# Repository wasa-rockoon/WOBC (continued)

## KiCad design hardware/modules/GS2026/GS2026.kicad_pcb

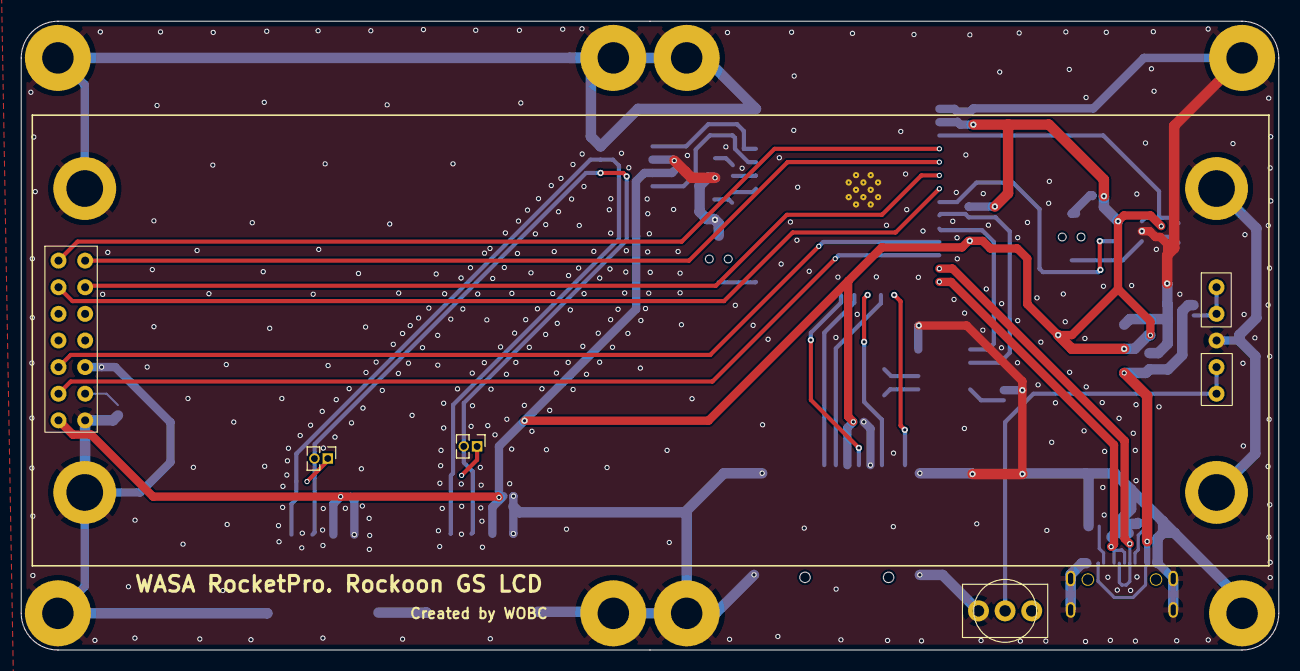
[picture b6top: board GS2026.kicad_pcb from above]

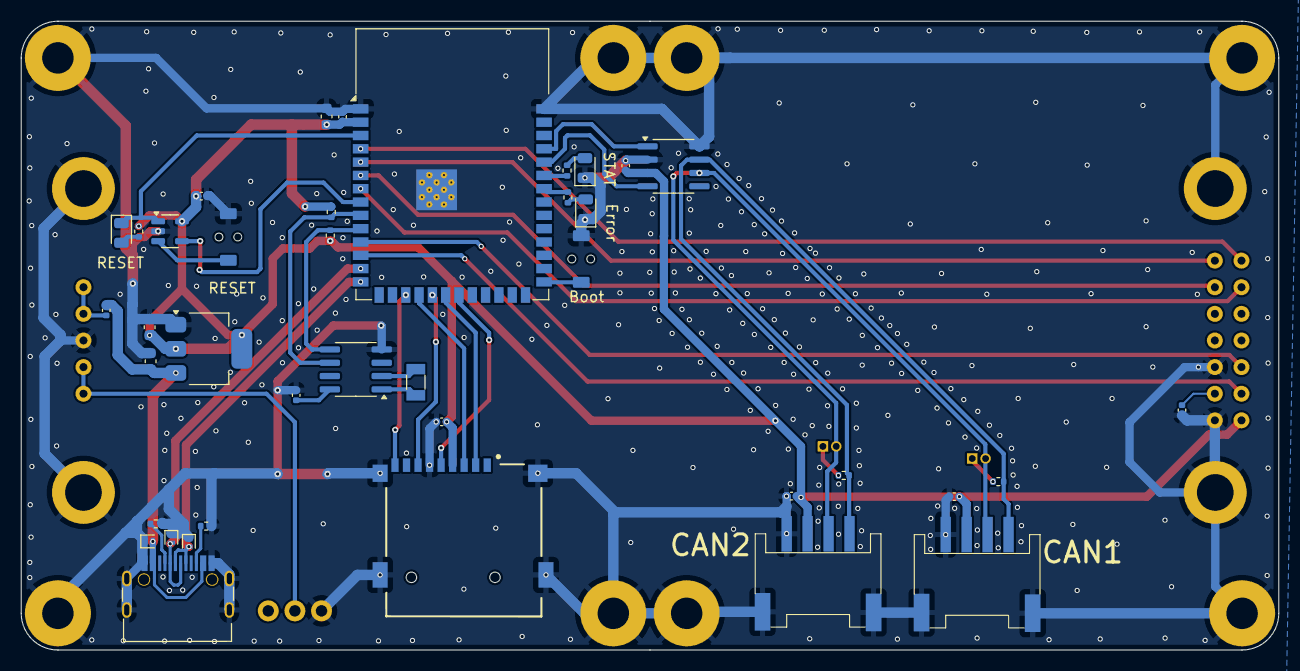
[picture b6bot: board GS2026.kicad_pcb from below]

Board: 2 copper layers, 120.0 x 60.0 mm, 44 parts (39 on the bottom side), 41 nets.

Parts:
B101: Board_2U_120x60
C101, C102, C203: 10uF; C_0603_1608Metric
C201, C202, C204, C301, C401, C602: 100nF; C_0402_1005Metric
C601: 10uF; C_0402_1005Metric
D201, D202, D203: 5V; D_SOD-882
D204: RESET; LED_0805_2012Metric
D205: ERROR; LED_0805_2012Metric
D206: STAT; LED_0805_2012Metric
J301, J401: Jumper; PinHeader_1x02_P1.27mm_Vertical
J302, J402: Conn_01x04_MountingPin; Grove_4P_L_SMD
MICRO_SD601: TF-01A
R201, R202: 5.1k; R_0402_1005Metric
R203, R204, R206: 470; R_0402_1005Metric
R205, R207: 10k; R_0402_1005Metric
R301, R401: 120; R_0402_1005Metric
R501: 1k; C_0402_1005Metric
R502: 68; C_0402_1005Metric
SW201: RESET_sw; TVAF06-A020B-R
SW202: RESET; TVAF06-A020B-R
SW501: sw1; ToggleSwitch
U101: AMS1117-3.3; SOT-223-3_TabPin2
U201: TPS3820; SOT-23-5
U202: SN65HVD230; SOIC-8_3.9x4.9mm_P1.27mm
U203: ESP32-S3-WROOM-1
U601: PCF8563T; SOIC-8_3.9x4.9mm_P1.27mm
USB201: USB_C_Receptacle_USB2.0; USB_C_TYPEC-301S-ACP16X7
Y601: Crystal; Crystal_SMD_3215-2Pin_3.2x1.5mm
lcd501: SC2004CSWB-XA-LB-G; SC2004CSWB

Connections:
+BATT: C602.2, U601.8 (VDD)
/CAN/CANH: J302.1, J402.1, R301.2, R401.2, U202.7 (CANH)
/CAN/CANL: J301.2, J302.2, J401.2, J402.2, U202.6 (CANL)
/ESP32S3/CAN_RX: U202.4 (R), U203.36 (U0RXD/GPIO44/CLK_OUT2)
/ESP32S3/CAN_TX: U202.1 (D), U203.37 (U0TXD/GPIO43/CLK_OUT1)
/ESP32S3/GPIO4/ADC1_CH3: U203.4 (GPIO4/TOUCH4/ADC1_CH3), lcd501.14 (DB7)
/ESP32S3/GPIO5/ADC1_CH4: U203.5 (GPIO5/TOUCH5/ADC1_CH4), lcd501.13 (DB6)
/ESP32S3/GPIO6/ADC1_CH5: U203.6 (GPIO6/TOUCH6/ADC1_CH5), lcd501.11 (DB4)
/ESP32S3/GPIO7/ADC1_CH6: U203.7 (GPIO7/TOUCH7/ADC1_CH6), lcd501.12 (DB5)
/ESP32S3/GPIO8/ADC1_CH7: U203.12 (GPIO8/TOUCH8/ADC1_CH7/SUBSPICS1), lcd501.4 (RS)
/ESP32S3/GPIO9/ADC1_CH8: MICRO_SD601.CD1 (CD), U203.17 (GPIO9/TOUCH9/ADC1_CH8/FSPIHD/SUBSPIHD)
/ESP32S3/GPIO10/ADC1_CH9: MICRO_SD601.3 (CMD), U203.18 (GPIO10/TOUCH10/ADC1_CH9/FSPICS0/FSPIIO4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)
/ESP32S3/GPIO11: MICRO_SD601.7 (DAT0), U203.19 (GPIO11/TOUCH11/ADC2_CH0/FSPID/FSPIIO5/S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)
/ESP32S3/GPIO12: MICRO_SD601.2 (CD/DAT3), U203.20 (GPIO12/TOUCH12/ADC2_CH1/FSPICLK/FSPIIO6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)
/ESP32S3/GPIO13: MICRO_SD601.5 (CLK), U203.21 (GPIO13/TOUCH13/ADC2_CH2/FSPIQ/FSPIIO7/S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)
/ESP32S3/GPIO18: U203.11 (GPIO18/U1RXD/ADC2_CH7/CLK_OUT3), lcd501.6 (E)
/ESP32S3/I2C_SCL: R205.2, U203.9 (GPIO16/U0CTS/ADC2_CH5/XTAL_32K_N), U601.6 (SCL)
/ESP32S3/I2C_SDA: R207.2, U203.10 (GPIO17/U1TXD/ADC2_CH6), U601.5 (SDA)
/ESP32S3/USB_D+: D202.2 (A2), U203.14 (GPIO20/U1CTS/ADC2_CH9/CLK_OUT1/USB_D+), USB201.A6 (D+), USB201.B6 (D+)
/ESP32S3/USB_D-: D203.2 (A2), U203.13 (GPIO19/U1RTS/ADC2_CH8/CLK_OUT2/USB_D-), USB201.A7 (D-), USB201.B7 (D-)
/ESP32S3/WDI: U201.4 (WDI), U203.8 (GPIO15/U0RTS/ADC2_CH4/XTAL_32K_P)
GND: B101.GND, C101.2, C102.2, C201.1, C202.1, C203.1, C204.2, C301.1, C401.1, C601.2, C602.1, D201.1 (A1), D202.1 (A1), D203.1 (A1), D205.1 (K), D206.1 (K), J302.4, J302.MP (MountPin), J402.4, J402.MP (MountPin), MICRO_SD601.6 (VSS), MICRO_SD601.MP1 (SHIELD), MICRO_SD601.MP2 (SHIELD), MICRO_SD601.MP3 (SHIELD), MICRO_SD601.MP4 (SHIELD), R201.2, R202.2, R501.1, SW201.2, SW202.2, SW501.3 (C), U101.1 (GND), U201.2 (GND), U202.2 (GND), U202.8 (Rs), U203.1 (GND), U203.40 (GND), U203.41 (GND), U601.4 (VSS), USB201.A1 (GND), USB201.A12 (GND), USB201.B1 (GND), USB201.B12 (GND), USB201.S1 (SHIELD), lcd501.1 (VSS), lcd501.5 (R/W), lcd501.16, lcd501.GND
unnamed: D204.2 (A), R203.2
unnamed: D205.2 (A), R204.2
unnamed: D206.2 (A), R206.2
unnamed: J301.1, R301.1
unnamed: J401.1, R401.1
unnamed: SW501.2 (B), lcd501.17 (K)
unnamed: SW201.1, U201.3 (MR)
unnamed: SW202.1, U203.27 (GPIO0/BOOT)
unnamed: R204.1, U203.34 (MTDI/GPIO41/CLK_OUT1)
unnamed: R206.1, U203.35 (MTMS/GPIO42)
unnamed: U601.1 (OSCI), Y601.1
unnamed: U601.2 (OSCO), Y601.2
unnamed: R201.1, USB201.A5 (CC1)
unnamed: R202.1, USB201.B5 (CC2)
unnamed: R502.1, lcd501.15 (A)
unnamed: R501.2, lcd501.3 (Vo)
RESET: D204.1 (K), U201.1 (RESET), U203.3 (EN)
VBUS: C101.1, D201.2 (A2), R502.2, U101.3 (VI), USB201.A4 (VBUS), USB201.A9 (VBUS), USB201.B4 (VBUS), USB201.B9 (VBUS)
VDD: C102.1, C201.2, C202.2, C203.2, C204.1, C301.2, C401.2, C601.1, J302.3, J402.3, MICRO_SD601.4 (VDD), R203.1, R205.1, R207.1, U101.2 (VO), U201.5 (VDD), U202.3 (VCC), U203.2 (3V3), lcd501.2 (VDD)

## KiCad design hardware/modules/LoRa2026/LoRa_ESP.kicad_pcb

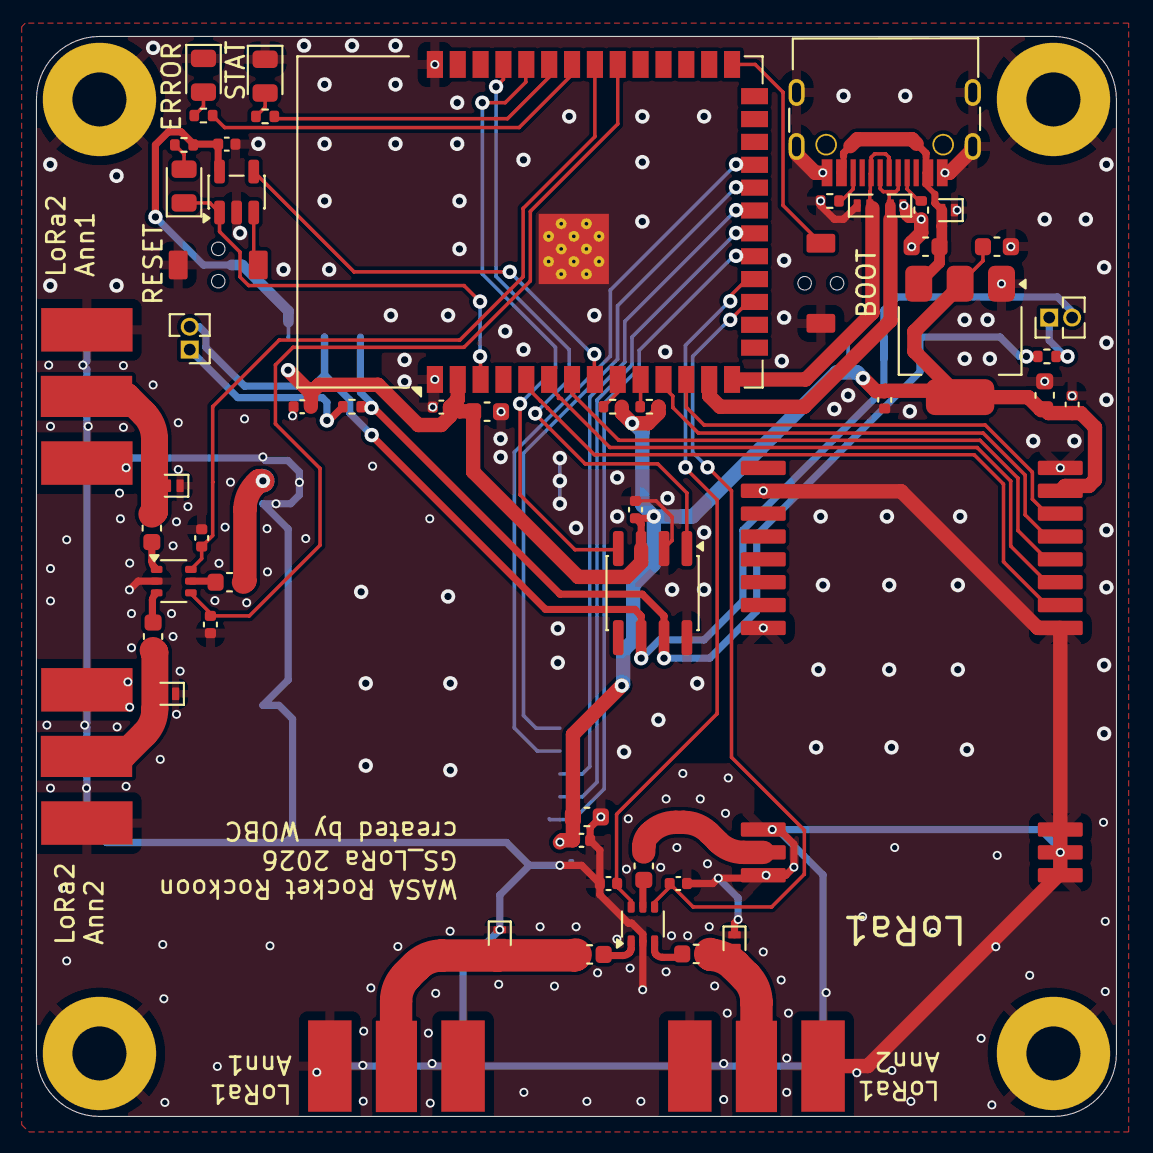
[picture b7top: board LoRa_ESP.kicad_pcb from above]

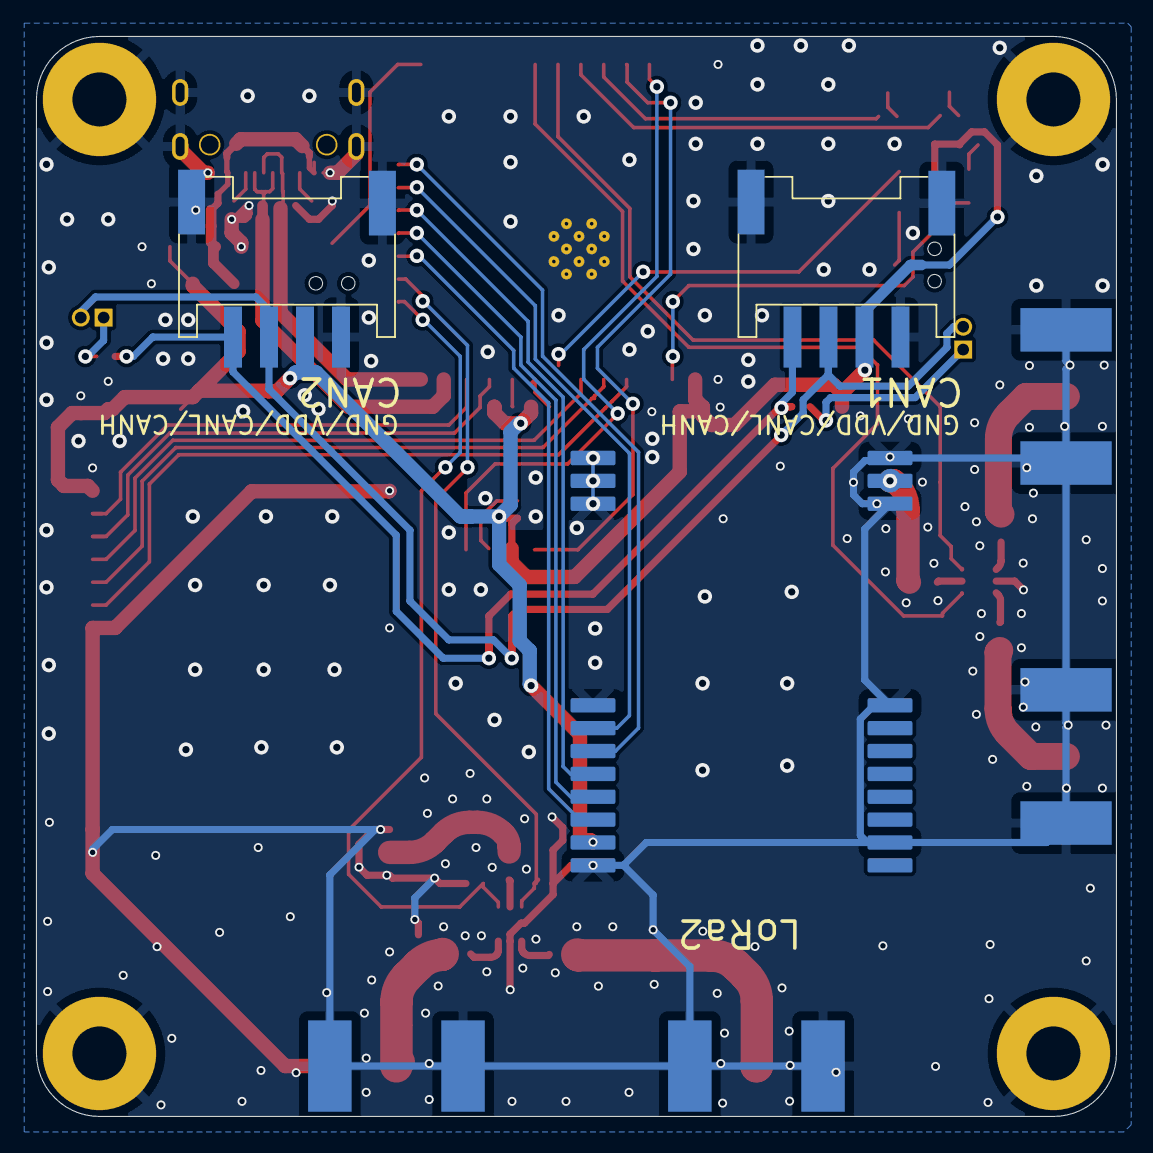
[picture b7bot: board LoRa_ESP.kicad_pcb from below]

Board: 2 copper layers, 60.0 x 60.0 mm, 60 parts (3 on the bottom side), 50 nets.

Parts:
BOOT: RESET; TVAF06-A020B-R
C101, C102, C306, C406: 10u; C_0603_1608Metric
C202, C602, C701, C702, C704: 100nF; C_0402_1005Metric
C301, C302, C305, C401, C402, C405: 100p; C_0603_1608Metric
C303, C304, C307, C403, C404, C407: 100n; C_0402_1005Metric
C703: 10uF; C_0603_1608Metric
D301, D302, D401, D402: ESD9B5.0ST5G; D_SOD-882
D701, D702, D703: 5V; D_SOD-882
D704: RESET; LED_0805_2012Metric
D705: ERROR; LED_0805_2012Metric
D706: STAT; LED_0805_2012Metric
J202, J602: Jumper; PinHeader_1x02_P1.27mm_Vertical
J203, J603: Conn_01x04_MountingPin; Grove_4P_L_SMD
J301, J302, J401, J402: SMA; SMA_aki
R202, R602: 120; R_0402_1005Metric
R701, R702: 5.1k; R_0402_1005Metric
R703, R704, R706: 470; R_0402_1005Metric
R705, R707: 10k; R_0402_1005Metric
RESET: RESET_sw; TVAF06-A020B-R
Switch301, Switch401: XA17-G4K1; SOT-363_SC-70-6
U101: AMS1117-3.3; SOT-223-3_TabPin2
U301, U401: E220-900T22S(JP)
U701: TPS3820; SOT-23-5
U702: SN65HVD230; SOIC-8_3.9x4.9mm_P1.27mm
U703: ESP32-S3-WROOM-1
USB701: USB_C_Receptacle_USB2.0; USB_C_TYPEC-301S-ACP16X7

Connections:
/ESP32core/CANH: J203.1, J603.1, R202.2, R602.2, U702.7 (CANH)
/ESP32core/CANL: J202.2, J203.2, J602.2, J603.2, U702.6 (CANL)
/ESP32core/CAN_RX: U702.4 (R), U703.36 (U0RXD/GPIO44/CLK_OUT2)
/ESP32core/CAN_TX: U702.1 (D), U703.37 (U0TXD/GPIO43/CLK_OUT1)
/ESP32core/GPIO5/ADC1_CH4: U401.5 (M0), U703.5 (GPIO5/TOUCH5/ADC1_CH4)
/ESP32core/GPIO6/ADC1_CH5: U401.6 (M1), U703.6 (GPIO6/TOUCH6/ADC1_CH5)
/ESP32core/GPIO7/ADC1_CH6: U401.7 (RXD), U703.7 (GPIO7/TOUCH7/ADC1_CH6)
/ESP32core/GPIO8/ADC1_CH7: U401.9 (AUX), U703.12 (GPIO8/TOUCH8/ADC1_CH7/SUBSPICS1)
/ESP32core/GPIO9/ADC1_CH8: C404.1, Switch401.4 (V1), U703.17 (GPIO9/TOUCH9/ADC1_CH8/FSPIHD/SUBSPIHD)
/ESP32core/GPIO10/ADC1_CH9: C403.1, Switch401.6 (V2), U703.18 (GPIO10/TOUCH10/ADC1_CH9/FSPICS0/FSPIIO4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)
/ESP32core/GPIO11: U301.9 (AUX), U703.19 (GPIO11/TOUCH11/ADC2_CH0/FSPID/FSPIIO5/S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)
/ESP32core/GPIO12: U301.8 (TXD), U703.20 (GPIO12/TOUCH12/ADC2_CH1/FSPICLK/FSPIIO6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)
/ESP32core/GPIO13: U301.7 (RXD), U703.21 (GPIO13/TOUCH13/ADC2_CH2/FSPIQ/FSPIIO7/S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)
/ESP32core/GPIO14: U301.5 (M0), U703.22 (GPIO14/TOUCH14/ADC2_CH3/FSPIWP/FSPIDQS/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)
/ESP32core/GPIO18: U401.8 (TXD), U703.11 (GPIO18/U1RXD/ADC2_CH7/CLK_OUT3)
/ESP32core/GPIO21: U301.6 (M1), U703.23 (GPIO21)
/ESP32core/GPIO39: C304.1, Switch301.4 (V1), U703.32 (MTCK/GPIO39/CLK_OUT3/SUBSPICS1)
/ESP32core/GPIO40: C303.1, Switch301.6 (V2), U703.33 (MTDO/GPIO40/CLK_OUT2)
/ESP32core/I2C_SCL: R705.2, U703.9 (GPIO16/U0CTS/ADC2_CH5/XTAL_32K_N)
/ESP32core/I2C_SDA: R707.2, U703.10 (GPIO17/U1TXD/ADC2_CH6)
/ESP32core/USB_D+: D702.2 (A2), U703.14 (GPIO20/U1CTS/ADC2_CH9/CLK_OUT1/USB_D+), USB701.A6 (D+), USB701.B6 (D+)
/ESP32core/USB_D-: D703.2 (A2), U703.13 (GPIO19/U1RTS/ADC2_CH8/CLK_OUT2/USB_D-), USB701.A7 (D-), USB701.B7 (D-)
/ESP32core/WDI: U701.4 (WDI), U703.8 (GPIO15/U0RTS/ADC2_CH4/XTAL_32K_P)
GND: BOOT.2, C101.2, C102.2, C202.1, C303.2, C304.2, C306.2, C307.2, C403.2, C404.2, C406.2, C407.2, C602.1, C701.1, C702.1, C703.1, C704.2, D301.1 (A1), D302.1 (A1), D401.1 (A1), D402.1 (A1), D701.1 (A1), D702.1 (A1), D703.1 (A1), D705.1 (K), D706.1 (K), J203.4, J203.MP (MountPin), J301.2 (Ext), J302.2 (Ext), J401.2 (Ext), J402.2 (Ext), J603.4, J603.MP (MountPin), R701.2, R702.2, RESET.2, Switch301.2 (GND), Switch401.2 (GND), U101.1 (GND), U301.1 (GND), U301.2 (GND), U301.3 (GND), U301.4 (GND), U301.11 (GND), U301.13 (GND), U301.19 (GND), U301.20 (GND), U301.22 (GND), U401.1 (GND), U401.2 (GND), U401.3 (GND), U401.4 (GND), U401.11 (GND), U401.13 (GND), U401.19 (GND), U401.20 (GND), U401.22 (GND), U701.2 (GND), U702.2 (GND), U702.8 (Rs), U703.1 (GND), U703.40 (GND), U703.41 (GND), USB701.A1 (GND), USB701.A12 (GND), USB701.B1 (GND), USB701.B12 (GND), USB701.S1 (SHIELD)
unnamed: C301.2, D301.2 (A2), J301.1 (In)
unnamed: C302.2, D302.2 (A2), J302.1 (In)
unnamed: C401.2, D401.2 (A2), J401.1 (In)
unnamed: C402.2, D402.2 (A2), J402.1 (In)
unnamed: D704.2 (A), R703.2
unnamed: D705.2 (A), R704.2
unnamed: D706.2 (A), R706.2
unnamed: J202.1, R202.1
unnamed: J602.1, R602.1
unnamed: C305.2, Switch301.5 (J1)
unnamed: C302.1, Switch301.3 (J2)
unnamed: C301.1, Switch301.1 (J3)
unnamed: C405.2, Switch401.5 (J1)
unnamed: C402.1, Switch401.3 (J2)
unnamed: C401.1, Switch401.1 (J3)
unnamed: C305.1, U301.21 (ANT)
unnamed: C405.1, U401.21 (ANT)
unnamed: RESET.1, U701.3 (MR)
unnamed: BOOT.1, U703.27 (GPIO0/BOOT)
unnamed: R704.1, U703.34 (MTDI/GPIO41/CLK_OUT1)
unnamed: R706.1, U703.35 (MTMS/GPIO42)
unnamed: R701.1, USB701.A5 (CC1)
unnamed: R702.1, USB701.B5 (CC2)
RESET: D704.1 (K), U701.1 (RESET), U703.3 (EN)
VBUS: C101.1, D701.2 (A2), U101.3 (VI), USB701.A4 (VBUS), USB701.A9 (VBUS), USB701.B4 (VBUS), USB701.B9 (VBUS)
VDD: C102.1, C202.2, C306.1, C307.1, C406.1, C407.1, C602.2, C701.2, C702.2, C703.2, C704.1, J203.3, J603.3, R703.1, R705.1, R707.1, U101.2 (VO), U301.10 (VDD), U401.10 (VDD), U701.5 (VDD), U702.3 (VCC), U703.2 (3V3)

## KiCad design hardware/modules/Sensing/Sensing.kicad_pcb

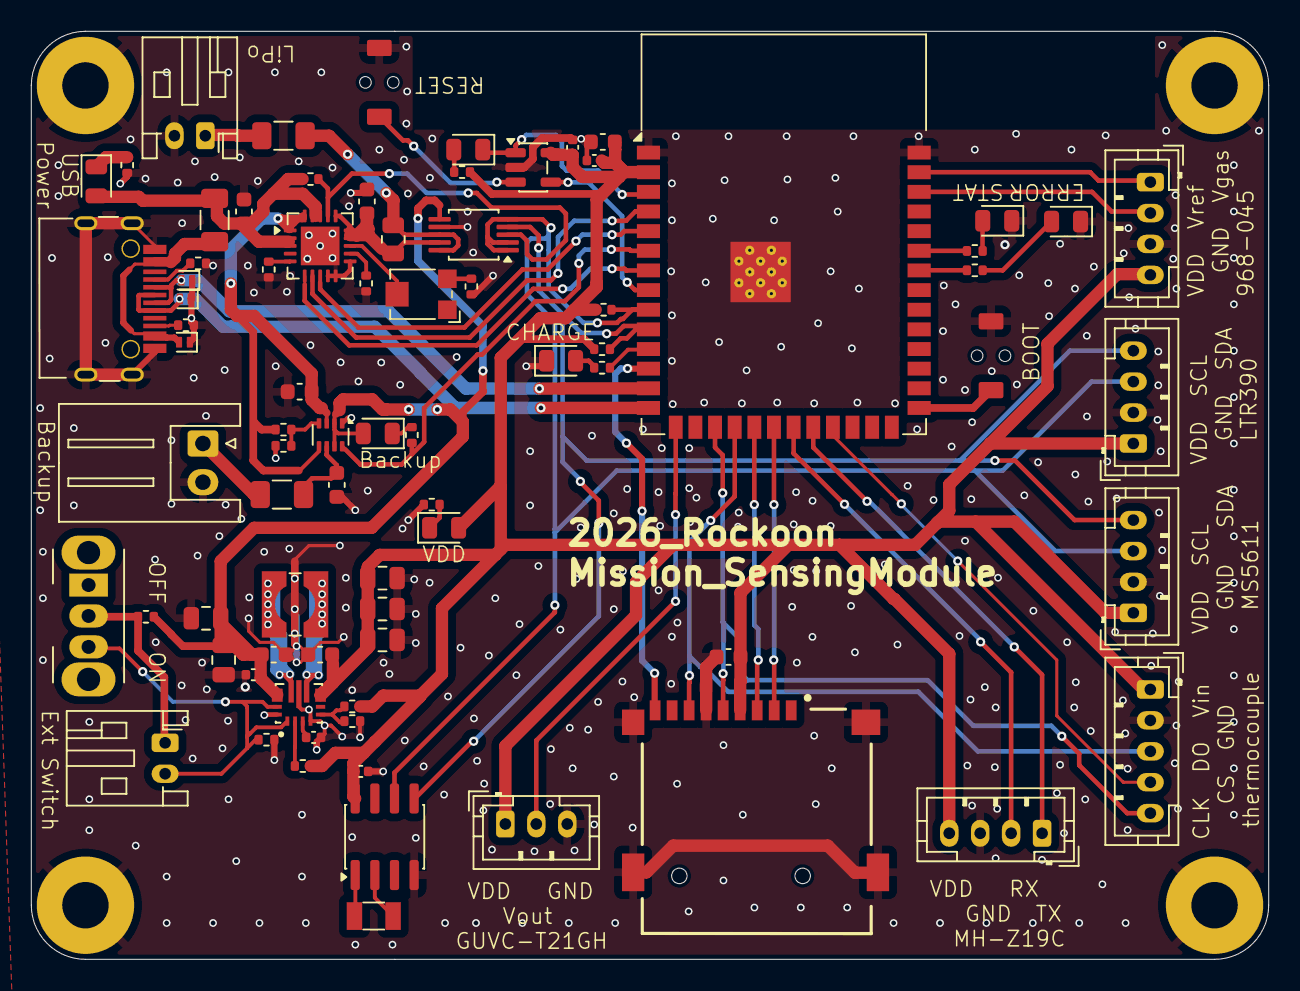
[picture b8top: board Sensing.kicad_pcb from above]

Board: 2 copper layers, 80.0 x 60.0 mm, 79 parts (0 on the bottom side), 61 nets.

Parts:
B101: Board_1U_60x60
C201, C203, C308, C309, C402: 100nF; C_0402_1005Metric
C202, C301, C302, C303, C306, C307, C310, C401: 10uF; C_0603_1608Metric
C304, C305, C311, C312, C313: 10uF; C_0805_2012Metric
D201, D202, D203: 5V; D_SOD-882
D204: RESET; LED_0805_2012Metric
D205: ERROR; LED_0805_2012Metric
D206: STAT; LED_0805_2012Metric
F301, F302, F303: Polyfuse; Fuse_1206_3216Metric
J101: MH-Z19C; JST_PH_B4B-PH-K_1x04_P2.00mm_Vertical
J102: 熱電対; JST_PH_B5B-PH-K_1x05_P2.00mm_Vertical
J103: GUVC-T21GH; JST_PH_B3B-PH-K_1x03_P2.00mm_Vertical
J104: MS5611 (MS5607); JST_PH_B4B-PH-K_1x04_P2.00mm_Vertical
J105: LTR390; JST_PH_B4B-PH-K_1x04_P2.00mm_Vertical
J106: 968-046; JST_PH_B4B-PH-K_1x04_P2.00mm_Vertical
J301: Battery; JST_XH_S2B-XH-A_1x02_P2.50mm_Horizontal
J302: Ext Switch; JST_PH_S2B-PH-K_1x02_P2.00mm_Horizontal
J303: LiPo; JST_PH_S2B-PH-K_1x02_P2.00mm_Horizontal
L301: L; L_Wuerth_WE-TPC-3816
LED301: USB Power; LED_0805_2012Metric
LED302: Backup; LED_0805_2012Metric
LED303: CHARGE; LED_0805_2012Metric
LED304: VDD; LED_0805_2012Metric
MICRO_SD401: TF-01A
R201, R202: 5.1k; R_0402_1005Metric
R203, R204, R206: 470; R_0402_1005Metric
R205, R207: 4.7k; R_0402_1005Metric
R301, R302, R308, R310, R316: 1k; R_0402_1005Metric
R303, R306, R307, R311, R313: 100k; R_0402_1005Metric
R304, R309: 10k; R_0402_1005Metric
R305, R315: 47k; R_0402_1005Metric
R312: 50mΩ; R_0805_2012Metric
R314: 15k; R_0402_1005Metric
RV301: 10k; Potentiometer_Bourns_TC33X_Vertical
SW201: RESET_sw; TVAF06-A020B-R
SW202: BOOT_sw; TVAF06-A020B-R
SW301: Power Switch; SW_Slide_SPDT_Angled_CK_OS102011MA1Q
U201: TPS3820; SOT-23-5
U202: ESP32-S3-WROOM-1
U301: MCP73871-1CC; QFN-20-1EP_4x4mm_P0.5mm_EP2.5x2.5mm
U302: TPS2116DRL; SOT-583-8
U303: TPS63070RNMR; VREG_TPS63070RNMR
U304: INA226; VSSOP-10_3x3mm_P0.5mm
U401: PCF8563T; SOIC-8_3.9x4.9mm_P1.27mm
USB201: USB_C_Receptacle_USB2.0; USB_C_TYPEC-301S-ACP16X7
Y401: Crystal; Crystal_SMD_3215-2Pin_3.2x1.5mm

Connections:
/ESP32S3/GPIO1/ADC1_CH0: J106.1, U202.39 (GPIO1/TOUCH1/ADC1_CH0)
/ESP32S3/GPIO2/ADC1_CH1: J106.2, U202.38 (GPIO2/TOUCH2/ADC1_CH1)
/ESP32S3/GPIO3/ADC1_CH2: J103.2, U202.15 (GPIO3/TOUCH3/ADC1_CH2)
/ESP32S3/GPIO4/ADC1_CH3: U202.4 (GPIO4/TOUCH4/ADC1_CH3), U301.7 (STAT2)
/ESP32S3/GPIO5/ADC1_CH4: U202.5 (GPIO5/TOUCH5/ADC1_CH4), U301.8 (STAT1/~LBO)
/ESP32S3/GPIO6/ADC1_CH5: R308.2, U202.6 (GPIO6/TOUCH6/ADC1_CH5), U302.8 (ST)
/ESP32S3/GPIO7/ADC1_CH6: U202.7 (GPIO7/TOUCH7/ADC1_CH6), U301.6 (~PG)
/ESP32S3/GPIO8/ADC1_CH7: MICRO_SD401.CD1 (CD), U202.12 (GPIO8/TOUCH8/ADC1_CH7/SUBSPICS1)
/ESP32S3/GPIO9/ADC1_CH8: J102.5, MICRO_SD401.5 (CLK), U202.17 (GPIO9/TOUCH9/ADC1_CH8/FSPIHD/SUBSPIHD)
/ESP32S3/GPIO10/ADC1_CH9: J102.3, MICRO_SD401.7 (DAT0), U202.18 (GPIO10/TOUCH10/ADC1_CH9/FSPICS0/FSPIIO4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)
/ESP32S3/GPIO11: MICRO_SD401.3 (CMD), U202.19 (GPIO11/TOUCH11/ADC2_CH0/FSPID/FSPIIO5/S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)
/ESP32S3/GPIO12: MICRO_SD401.2 (CD/DAT3), U202.20 (GPIO12/TOUCH12/ADC2_CH1/FSPICLK/FSPIIO6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)
/ESP32S3/GPIO18: R310.2, U202.11 (GPIO18/U1RXD/ADC2_CH7/CLK_OUT3)
/ESP32S3/GPIO21: J102.4, U202.23 (GPIO21)
/ESP32S3/USB_D+: D202.2 (A2), U202.14 (GPIO20/U1CTS/ADC2_CH9/CLK_OUT1/USB_D+), USB201.A6 (D+), USB201.B6 (D+)
/ESP32S3/USB_D-: D203.2 (A2), U202.13 (GPIO19/U1RTS/ADC2_CH8/CLK_OUT2/USB_D-), USB201.A7 (D-), USB201.B7 (D-)
/ESP32S3/VUSB: D201.2 (A2), F301.1, USB201.A4 (VBUS), USB201.A9 (VBUS), USB201.B4 (VBUS), USB201.B9 (VBUS)
/ESP32S3/WDI: U201.4 (WDI), U202.8 (GPIO15/U0RTS/ADC2_CH4/XTAL_32K_P)
/RX: J101.2, U202.21 (GPIO13/TOUCH13/ADC2_CH2/FSPIQ/FSPIIO7/S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)
/SCL: J104.3, J105.3, R205.2, U202.9 (GPIO16/U0CTS/ADC2_CH5/XTAL_32K_N), U304.1 (A1), U304.2 (A0), U304.5 (SCL), U401.6 (SCL)
/SDA: J104.4, J105.4, R207.2, U202.10 (GPIO17/U1TXD/ADC2_CH6), U304.4 (SDA), U401.5 (SDA)
/TX: J101.1, U202.22 (GPIO14/TOUCH14/ADC2_CH3/FSPIWP/FSPIDQS/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)
GND: B101.GND, C201.1, C202.1, C203.2, C301.2, C302.2, C303.2, C304.2, C305.2, C306.2, C307.2, C308.2, C309.2, C310.2, C311.2, C312.2, C313.2, C401.2, C402.1, D201.1 (A1), D202.1 (A1), D203.1 (A1), D205.1 (K), D206.1 (K), J101.3, J102.2, J103.3, J104.2, J105.2, J106.3, J301.2, J303.2, LED303.1 (K), MICRO_SD401.6 (VSS), MICRO_SD401.MP1 (SHIELD), MICRO_SD401.MP2 (SHIELD), MICRO_SD401.MP3 (SHIELD), MICRO_SD401.MP4 (SHIELD), R201.2, R202.2, R301.2, R302.2, R303.2, R304.1, R305.1, R311.2, R314.1, R316.2, SW201.2, SW202.2, U201.2 (GND), U202.1 (GND), U202.40 (GND), U202.41 (GND), U301.9 (~TE), U301.10 (V_{SS}), U301.11 (V_{SS}), U301.21 (V_{SS}), U302.1 (GND), U303.4 (GND), U303.10 (PGND), U303.15 (VSEL), U304.7 (GND), U401.4 (VSS), USB201.A1 (GND), USB201.A12 (GND), USB201.B1 (GND), USB201.B12 (GND), USB201.S1 (SHIELD)
unnamed: D204.2 (A), R203.2
unnamed: D205.2 (A), R204.2
unnamed: D206.2 (A), R206.2
unnamed: F302.1, J301.1
unnamed: J302.1, R309.2, SW301.2 (B)
unnamed: J302.2, R311.1, SW301.3 (C), U303.1 (PS/SYNC), U303.14 (EN)
unnamed: F303.1, J303.1
unnamed: C301.1, F301.2, LED301.2 (A), R306.1, U301.2 (VPCC), U301.3 (SEL), U301.18 (IN), U301.19 (IN)
unnamed: LED301.1 (K), R301.1
unnamed: C304.1, C305.1, C307.1, C308.1, LED302.2 (A), R309.1, U302.2 (VOUT), U302.7 (VOUT), U303.12_13 (VIN), U304.6 (VS)
unnamed: LED302.1 (K), R308.1
unnamed: LED303.2 (A), R310.1
unnamed: LED304.1 (K), R316.1
unnamed: R302.1, RV301.3
unnamed: SW201.1, U201.3 (MR)
unnamed: SW202.1, U202.27 (GPIO0/BOOT)
unnamed: R204.1, U202.34 (MTDI/GPIO41/CLK_OUT1)
unnamed: R206.1, U202.35 (MTMS/GPIO42)
unnamed: R306.2, U301.17 (CE), U304.3 (~Alert)
unnamed: RV301.2, U301.13 (PROG1)
unnamed: R303.1, U301.12 (PROG3)
unnamed: R304.2, U301.5 (THERM)
unnamed: C306.1, R312.1, U301.14 (V_{BAT}), U301.15 (V_{BAT}), U301.16 (V_{BAT_SENSE}), U304.9 (Vin-)
unnamed: C303.1, R307.1, U301.1 (OUT), U301.20 (OUT), U302.3 (VIN1), U302.5 (MODE)
unnamed: R305.2, R307.2, U302.4 (PR1)
unnamed: C302.1, F302.2, U302.6 (VIN2)
unnamed: R314.2, R315.1, U303.5 (FB)
unnamed: L301.1, U303.11 (L1)
unnamed: L301.2, U303.9 (L2)
unnamed: R313.2, U303.2 (PG)
unnamed: C309.1, U303.3 (VAUX)
unnamed: F303.2, R312.2, U304.8 (Vbus), U304.10 (Vin+)
unnamed: U401.1 (OSCI), Y401.1
unnamed: U401.2 (OSCO), Y401.2
unnamed: R201.1, USB201.A5 (CC1)
unnamed: R202.1, USB201.B5 (CC2)
RESET: D204.1 (K), U201.1 (RESET), U202.3 (EN)
VDD: C201.2, C202.2, C203.1, C310.1, C311.1, C312.1, C313.1, C401.1, C402.2, J101.4, J102.1, J103.1, J104.1, J105.1, J106.4, LED304.2 (A), MICRO_SD401.4 (VDD), R203.1, R205.1, R207.1, R313.1, R315.2, U201.5 (VDD), U202.2 (3V3), U303.7_8 (VOUT), U401.8 (VDD)

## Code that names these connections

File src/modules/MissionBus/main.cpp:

// #define NDEBUG

#include <library/wobc.h>
#include <components/LiPoPower/lipo_power.h>
#include <components/LoRa/lora.h>
#include <components/Pressure/pressure.h>
#include <components/IMU/IMU.h>
#include <components/GPS/gps.h>
#include <components/Logger/logger.h>
#include <components/Telemeter/telemeter.h>
#include <SPI.h>

#define SPI0_SCK_PIN 5
#define SPI0_MOSI_PIN 1
#define SPI0_MISO_PIN 2
#define SPI0_CS_PIN 4

#define SD_INSERTED_PIN 6
#define SDCARD_MOSI_PIN SPI0_MOSI_PIN
#define SDCARD_MISO_PIN SPI0_MISO_PIN
#define SDCARD_SS_PIN SPI0_CS_PIN
#define SDCARD_SCK_PIN SPI0_SCK_PIN

#define ST 8
#define PG 11
#define STAT1 10
#define STAT2 -1
#define HEAT 48
#define CHARGELED -1
#define TEMP 9

#define LORA_CHANNEL 37
#define LORA_TX_PIN 13
#define LORA_RX_PIN 12
#define LORA_AUX_PIN 21
#define LORA_M0_PIN 14
#define LORA_M1_PIN 18

// GS-compatible setting; verify against the MissionBus board wiring.
#define CAN_RX_PIN 44
#define CAN_TX_PIN 43

constexpr uint8_t module_id = 0x4D;
constexpr uint8_t unit_id = 0x62;

HardwareSerial lora_serial(1);
core::CANBus can_bus(CAN_RX_PIN, CAN_TX_PIN);
core::SerialBus serial_bus(Serial);
// Use the same telemetry server as GS, including IGN and sensor telemetry.
component::Telemeter telemeter(true);

component::LiPoPower power(Wire, ST, PG, STAT1, STAT2, HEAT, CHARGELED, TEMP, unit_id, 1);
component::LoRa lora(LORA_AUX_PIN, LORA_M0_PIN, LORA_M1_PIN, LORA_TX_PIN, LORA_RX_PIN, LORA_CHANNEL, 0);
component::Logger logger(SPI, SPI0_CS_PIN, SD_INSERTED_PIN);
component::Pressure pressure(Wire, unit_id);
component::IMU9 imu(Wire, unit_id, 10, IMU_DATA, IMU_BMI_BMM);
component::GPS gps(38, 39, 9600, unit_id);

interface::WatchIndicator<unsigned> status_indicator(42, kernel::packetCount());
interface::WatchIndicator<unsigned> error_indicator(41, kernel::errorCount());

class Main : public process::Component {
public:
    Main() : process::Component("main", 0x00) {}
    kernel::Listener my_listener_;

    void setup() override {
        my_listener_.telemetry(); 
        listen(my_listener_, 8);
    }

    void loop() override {
        while (my_listener_) {
            const wcpp::Packet packet = my_listener_.pop();
            auto im = packet.find("Im");
            if (!im) {
                wcpp::Packet lorapacket = newPacket(64);
                if (!lorapacket) continue;
                lorapacket.command(lora.send_command_id, lora.component_id_base + 0);
                lorapacket.append("Pa").setPacket(packet);
                sendPacket(lorapacket);
            }
        }
    }

} main_;

void setup() {
    Serial.begin(115200);
    kernel::setUnitId(unit_id);
    if (!kernel::begin(module_id, true)) return;

    Serial0.setPins(4, 5);
    Wire.begin(17, 16);

    SPI.begin(SDCARD_SCK_PIN, SDCARD_MISO_PIN, SDCARD_MOSI_PIN, SDCARD_SS_PIN);

    delay(1000); 

    status_indicator.begin();
    status_indicator.blink_on_change();

    error_indicator.begin();
    error_indicator.set(true);

    
    imu.begin();
    can_bus.begin();
    serial_bus.begin();
    telemeter.begin();
    power.begin();
    lora.begin();
    pressure.begin();
    gps.begin();
    logger.begin();
    main_.begin();

    error_indicator.set(false);
    error_indicator.blink_on_change(100);
}

void loop() {
    status_indicator.update();
    error_indicator.update();
}

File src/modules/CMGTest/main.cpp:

#include <Arduino.h>
#include <Wire.h>
#include <SPI.h>
#include <library/wobc.h>
#include <components/Logger/logger.h>
#include <components/IMU/IMU.h>
#include <components/Pressure/pressure.h>
#include <components/Heater/Heater.h>
#include <components/Servo/LogServo.h>
//#include <components/MotorControl/MotorControl.h>
#include <components/LiPoPower/lipo_power.h>
#include <components/PowerMeasure/PowerMeasure.h>


#define I2C_SCL_PIN 16
#define I2C_SDA_PIN 17
#define I2C_freq 400000

#define SPI0_SCK_PIN 12
#define SPI0_MOSI_PIN 11
#define SPI0_MISO_PIN 13
#define SPI0_CS_PIN 10

#define SD_INSERTED_PIN 9
#define SDCARD_MOSI_PIN SPI0_MOSI_PIN
#define SDCARD_MISO_PIN SPI0_MISO_PIN
#define SDCARD_SS_PIN SPI0_CS_PIN
#define SDCARD_SCK_PIN SPI0_SCK_PIN

#define ST 4
#define PG 5
#define STAT1 7
#define STAT2 6
#define HEAT 48
#define CHARGELED 18
#define TEMP 47

core::SerialBus serial_bus(Serial); 

constexpr uint8_t module_id = 0x45;
constexpr uint8_t unit_id = 0x66;

component::Logger logger(SPI, SPI0_CS_PIN, -1, 10.0);
component::IMU9 imu(Wire, unit_id, 100, IMU_DATA_WITH_KALMAN_6, IMU_ICM_MMC);
//component::Heater heater(Wire, unit_id, 1);
//component::LogServo servo(12, 34, unit_id, WITH_READANGLE, 50);
component::Pressure pressure(Wire, unit_id, 1);
//component::MotorControl motor(2, 3, unit_id, 1000, 50);
component::LiPoPower power(Wire, ST, PG, STAT1, STAT2, HEAT, CHARGELED, TEMP, unit_id, 1);
component::PowerMeasure power_measure(Wire, unit_id, 10);

interface::WatchIndicator<unsigned> status_indicator(42, kernel::packetCount());
interface::WatchIndicator<unsigned> error_indicator(41, kernel::errorCount());

class Main : public process::Component {
public:
    Main() : process::Component("Main", 0x00) {}
    kernel::Listener my_listener_;
    kernel::Listener heartbeat_;
  
    void setup() override {
        LOG("CMG Task: Setup started"); 
        my_listener_.telemetry(); 
        listen(my_listener_, 8);
        heartbeat_.component(0x4D);
        listen(heartbeat_,1);
        LOG("CMG Task: loop starts"); 
    }

    void loop() override {
        static uint32_t start_time = millis();
        if (millis() - start_time > 1200000) {
            request_file_split.store(true);
            start_time = millis();
        }
        delay(100);
        // while (my_listener_) { //main向けのログがあれば実行
            float Ax = 0.1;
            float Ay = 0.2;
            float Az = 0.3;
            float Gx = 0.4;
            float Gy = 0.5;
            float Gz = 0.6;
            float Mx = 0.7;
            float My = 0.8;
            float Mz = 0.9;
            wcpp::Packet packet = my_listener_.pop();
            wcpp::Packet new_packet = newPacket(128);
            new_packet.telemetry('C', component_id(), unit_id, 0xFF, 1234);
            new_packet.append("Ts").setInt((int)millis());
            new_packet.append("Ax").setFloat32(Ax);
            new_packet.append("Ay").setFloat32(Ay);
            new_packet.append("Az").setFloat32(Az);
            new_packet.append("Gx").setFloat32(Gx);
            new_packet.append("Gy").setFloat32(Gy);
            new_packet.append("Gz").setFloat32(Gz);
            new_packet.append("Mx").setFloat32(Mx);
            new_packet.append("My").setFloat32(My);
            new_packet.append("Mz").setFloat32(Mz);

            sendPacket(new_packet);

            //}
        }
} main_;

void setup() {
    Serial.begin(115200);
    kernel::setUnitId(unit_id);
    if (!kernel::begin(module_id, true)) return;

    //wobc::beginSPI(SPI, SDCARD_SCK_PIN, SDCARD_MISO_PIN, SDCARD_MOSI_PIN, SDCARD_SS_PIN);
    wobc::beginI2C(Wire, I2C_SDA_PIN, I2C_SCL_PIN, I2C_freq);
    serial_bus.begin(); 

    delay(1000);

    status_indicator.begin();
    status_indicator.blink_on_change();

    error_indicator.begin();
    error_indicator.set(true);
    
    logger.begin();
    imu.begin(); 
    //heater.begin();
    //servo.begin();
    pressure.begin();
    main_.begin();
    //motor.begin();
    power.begin();
    power_measure.begin();

    error_indicator.set(false);
    error_indicator.blink_on_change(100);
}

void loop() {
    status_indicator.update();
    error_indicator.update();
}

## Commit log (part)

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2025-02-26 新しいバージョンで保存
2025-03-01 [env]:CMを追加 buildはまだfailedのまま
2025-03-01 各種[env]を追加
2025-03-17 Revert "各種[env]を追加"
    This reverts commit 06dd88b1f6881fce08624e657637abe75ff9de40.
2025-05-02 Reapply "各種[env]を追加"
    This reverts commit ccc804d16412df13b768156cc56868a79d96f36c.
2025-06-20 元に戻したはず
2025-06-20 とりあえず
2025-06-24 新しくブランチをつくってマージしたい
2025-06-24 Revert "Merge branch 'feature/Trackersrc2' of https://github.com/wasa-rockoon/WOBC into feature/Trackersrc"
    This reverts commit b5165213b03911a8cbeba14fce0be4171c696dd6, reversing
    changes made to ba3467030067534b9f530ec432d8cbef88b83492.
2025-06-24 GPSでUT，Pressureで気圧高度とれるようになりました．
2025-07-22 海面気圧変更
2025-07-23 原因探索
2025-07-29 コンポーネントの修正
2025-07-31 回路図にpressure追加
2025-07-31 回路図は一旦終了
2025-07-31 mosfetの配置しなおし
2025-07-31 bmeの配置と諸々の調整
2025-08-01 component側の修正
2025-08-01 配線幅修正
2025-08-03 CAN周り終端抵抗の位置とか一部変更
2025-08-03 コネクタをXH，PH→XAに変更
2025-08-03 env作ってbuildするところまで
2025-08-05 ガーバーファイル出力
2025-08-06 loadcell消してIMUとPressure追加
2025-08-06 コネクタを変更 CAN周りをちょっと修正
2025-08-18 IMU2 コンポーネントを作りました
2025-08-18 RCS基板におきました
2025-08-19 BMM150のフットプリントのクリアランスを変更してパットを置けるようにしました．
2025-08-20 9DoFをIMU2に差し替え
2025-08-20 BMM150のフットプリント編集
2025-08-20 ちょっと修正
2025-08-20 RCS 変更しました。
2025-08-20 IGNには常時給電する仕様に変更，GPIO3を開けた，終端抵抗は使用上終端にならないので削除
2025-08-20 ガーバーファイルを出力しました。
2025-08-21 ガーバーファイル出力し直し
2025-08-22 330kΩのLCSC変更
2025-08-22 配線されてないかったとこを修正．．．
2025-08-22 LCSC確認後，再度ガーバーファイル出力
2025-08-22 もっかいガーバーファイル出力
2025-08-26 lora動きました
2025-09-04 センチ秒が取れるようにしました．
2025-09-07 俺のスマホのテザリングのパスワードと，ws_host, urlの更新
2025-09-07 応急処置でコンポーネントのcppファイルでタイムスタンプとるようにしました．
2025-09-08 env:MissionBusを追加
2025-09-08 ピン番号設定
2025-09-08 電源と気圧は取れる
2025-09-08 SDカードのピン割り当て修正
2025-09-09 IMUコンポーネントをかるく
2025-09-09 ちょっと追記
2025-09-10 値とれるようにはなった
2025-09-10 IMUいったん終了
2025-09-11 lora.begin()をコメントアウト
2025-09-11 タイムスタンプコメントアウト
2025-09-14 とりあえず2D
2025-09-15 3Dバージョン
2025-09-15 欠損値を除外できるように修正
2025-09-26 地図を見やすくした
2025-11-03 FCSの作成
2025-11-03 FCS作成
2025-11-03 バナナ一世がブランチを作成しました！
2025-11-03 ブランチ作成
2025-11-03 FCSのKiCad作成
2025-11-03 GPSの相対時間コメントアウト
2026-01-29 種コン用 ゴリ電基板作成
2026-01-29 ピン配置
2026-01-29 SAM-M8Qのシンボル，フットプリントを追加
2026-01-29 プルアップ抵抗
2026-02-02 Servoを追加
2026-02-05 途中経過
2026-02-05 GPS,BME追加
2026-02-05 回路図まで
2026-02-05 footprintなど
2026-02-06 配置微調整
2026-02-08 電源関係おいた
2026-02-08 LoRa,GPS周りの配線
2026-02-08 充放電icとlipo，VBUS周り
2026-02-08 ちょい直し
2026-02-08 置き直し一旦終わり…？
2026-02-09 ちょっと変更
2026-02-09 電源回り配線
2026-02-09 大体配置終了
2026-02-09 BMM150追加 配置
2026-02-10 サーボ用LiPoの向きを反転
2026-02-11 軸のシルクを追加
2026-02-11 チェック
2026-02-12 シルク追加
2026-02-13 GOLIDENのシルク書き忘れ...ごめんなさい
2026-02-13 フットプリント修正
2026-02-13 ベタ塗り直してガーバー出力
2026-02-14 もう一回ガーバー出力
2026-02-14 白黒チェックのコードを追加
2026-02-14 micropython版の回転数計のコードを追加
2026-02-14 picoのメモリをすべてクリアするnuke.uf2を追加
2026-02-15 docsに色々追記していくためのブランチを作りました．
2026-02-16 ２号機の配線を回路図にしている
2026-02-16 rp2350向けにビルドできるようにplatformio.iniに追記 ただしcan通信はrp2350に未対応 CMG用テストコードを追加
2026-02-17 CMGのテストコードを入れる場所を修正
2026-02-18 CMG用コードにピン配置を書き込み
2026-02-18 CMG用コードに使えるコンポーネントを探してインクルード
2026-03-01 ゴリ電ようのブランチを追加
2026-03-01 IMUのライブラリを追加し，コンパイルが通るようにした
2026-03-01 IMUの値をシリアルモニタに出力
2026-03-01 LoRaの確認用 未完了
2026-03-02 パケットつけてみた
2026-03-02 LoRa 続き
2026-03-02 コンパイルエラー解消
2026-03-02 ジャイロが整数になってしまう問題の解決
2026-03-02 LoRa 更新
2026-03-03 LoRaのチャンネルは３でした，気を付けましょう
2026-03-03 GPSをとりあえず有効にしてみました．動くかはまだわからない
2026-03-04 IMU取得はこれでいける
2026-03-04 50Hzでギリ耐え
2026-03-04 LoRaのbuildが通らなかったので，ちょっと変更
2026-03-04 100HzでSDにはデータ保存できている
2026-03-04 GPSのボーレートはちゃんと確認しましょう！
2026-03-04 iniのファイルからenv:MissionBusが消えていたので復活させました．とりあえず，ビルドは通りますが，IMUがAUX接続していないので使えません
2026-03-06 タイマーレートを明示
2026-03-06 誤差角度とか出せるようになった．IMUのデータがLoRaで送信されない以外は問題ない
2026-03-07 .mdファイルで備忘録的なものを作れたらとおもい，手始めに一つ作ってもらいました．
2026-03-07 PCから基板の通信について知りたい
2026-03-07 再度修正
2026-03-07 テンプレートを作ってみました．
2026-03-07 ちょっと更新
2026-03-07 マイナーチェンジ
2026-03-07 マイナーチェンジ２
2026-03-07 env:rp2024をちょっと変更
2026-03-07 名前変更
2026-03-07 pakect::telemetryについて
2026-03-07 電源まわりの情報はSDにだけ保存されるようにしました
2026-03-07 GPSの小数点の桁数を減らした
2026-03-07 GPSとLiPoのレートを１に変更 制御がうまく言っていると思われているコードにコメントアウトを付け足したものに変更
2026-03-07 色々修正
2026-03-07 なんかわからんがLoRaのビルド通った
2026-03-07 LipopowerがLoRaで送信されないように
2026-03-07 もうtrackerのmain.cppだけ変更した
2026-03-10 本番の時書き込んだもの
2026-03-10 画像を追加
2026-03-29 READMEに色々追記
2026-03-29 Fix typo in title of GitHub Copilot manual
    修正
2026-03-29 入力にあわせる
2026-03-29 Fix typo in title of GitHub Copilot manual
2026-03-29 LoRaのbuildが通らない件について作業ログ
2026-04-03 認証後のCopilot Pro有効化の手順について更新
2026-04-05 ラズパイに書き込めない問題について
2026-04-06 ・loggerとcanをRP2350でもビルドが通るようにした ・loggerは100Hzで回せるようにした
2026-04-06 ・CMG用にIMUとSDカードが動かせるようにした ・SPIとI2Cの初期化をESPでもRP2350でも同様にできるようにした
2026-04-08 ログ関連を追記
2026-04-09 logger自身のログが取れるように変更
2026-04-10 Initial plan
2026-04-10 CMGに気圧の取得機能を追加
2026-04-11 Madgwickフィルターの試作品
2026-04-12 互換性を保ちつつ、Madgwickフィルタを適用する機能をIMUコンポーネントに追加
2026-04-12 SDカードの保存タスクをCore0のみにやらせることで安定性を上げる試み
2026-04-28 GPSのコンフリクトを解決 タスクのコア指定ができるようにしてみた ↑動作確認はしていない
2026-05-04 IMUに互換性を保ちながらMMC5603用コードを追加
2026-05-04 MMC5603の値の読み方を修正
2026-05-06 MMC5603が再定義エラーを起こさないように修正
2026-05-06 ICM42688のライブラリを拾ってきて使える形に小修整
2026-05-06 カルマンフィルタを実装（動作確認済）
2026-05-06 IMUコンポーネントがICM42688に対応（動作確認はまだ） カルマンフィルタ適用機能を追加
2026-05-07 IGNのファイルを作った
2026-05-07 RP2040でcanのビルドが通るように小修整
2026-05-07 lipopowersimpleで電圧取れるようにした
2026-05-07 GSでGPS取れた
2026-05-07 GPSコンポーネントを使い方を変えずにRP2350でもビルドできるようにした
2026-05-07 RPシリーズでLoraが使えるようにもどした
2026-05-07 IGN基板でWOBCが動いた
2026-05-09 IGNでCAN送れない
2026-05-09 ICM42688を動作させるために修正
2026-05-09 I2C初期化の被りを修正
2026-05-12 CANが何となく進捗 RCS-IGN間のCANには成功 LoRaのボーレートを修正
2026-05-12 docs更新
2026-05-13 タコメーターのesp版を作成しました
2026-05-18 CMGのKicadファイルを作成
2026-05-18 ちょっとだけ回路図
2026-05-18 2026基板のデータ作成
2026-05-18 IMU3（ICM42688＆MMC5633）のコンポーネントを作成
2026-05-19 IMUを編集，MotorControl/Flightpinコンポーネントを追加
2026-05-20 Heaterコンポーネントを追加
2026-05-20 Flightpin・HeaterコンポーネントをIGNにも追加
2026-05-21 Flightpin,Heaterコンポーネントを追加
2026-05-25 動作を改善
2026-06-12 動作の安定性を上げるために小修整
2026-06-12 loggerの挙動を改善
2026-06-16 SDカードの初期化に失敗することがある不具合を修正
2026-06-18 メモ書き
2026-06-18 パケット送信の方法についてまとめた
2026-06-18 データの準備ができたかのステータスレジスタを読んでからデータを読む処理を追加
2026-06-18 任意のタイミングでmainからloggerのログファイルを分割できるようにした 後方互換性を確保し，IMUのみ他環境に持って行っても多分動くようにした
2026-06-22 点火回路を色々変更
2026-06-25 コメント記入
2026-06-25 FatherBoard（仮）の回路図までやった
2026-06-25 ちょっと配線をしようとして諦めた
2026-06-26 いろいろ
2026-06-27 レイアウトまで行ける？ところまでやった
